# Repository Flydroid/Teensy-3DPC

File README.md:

# Teensy-3DPC 
is a 3D Printer Controller Board based on the Teensy 3.5 or 3.6.

Schematic and Layout are done in Eagle 

The hardware is still in development and this git used for sharing the development proceess.

#### Contribution to Think3dPrint3d and Esher3d for the DuetWifi Design on which, the Teensy-3DPC is partly based:

"Based on the DuetWifi by Think3dPrint3d and Esher3d, see www.duet3d.com for the original DuetWifi information. This reproduction/modification is not endorsed or supported in any way by Think3dPrint3d or Escher3d".

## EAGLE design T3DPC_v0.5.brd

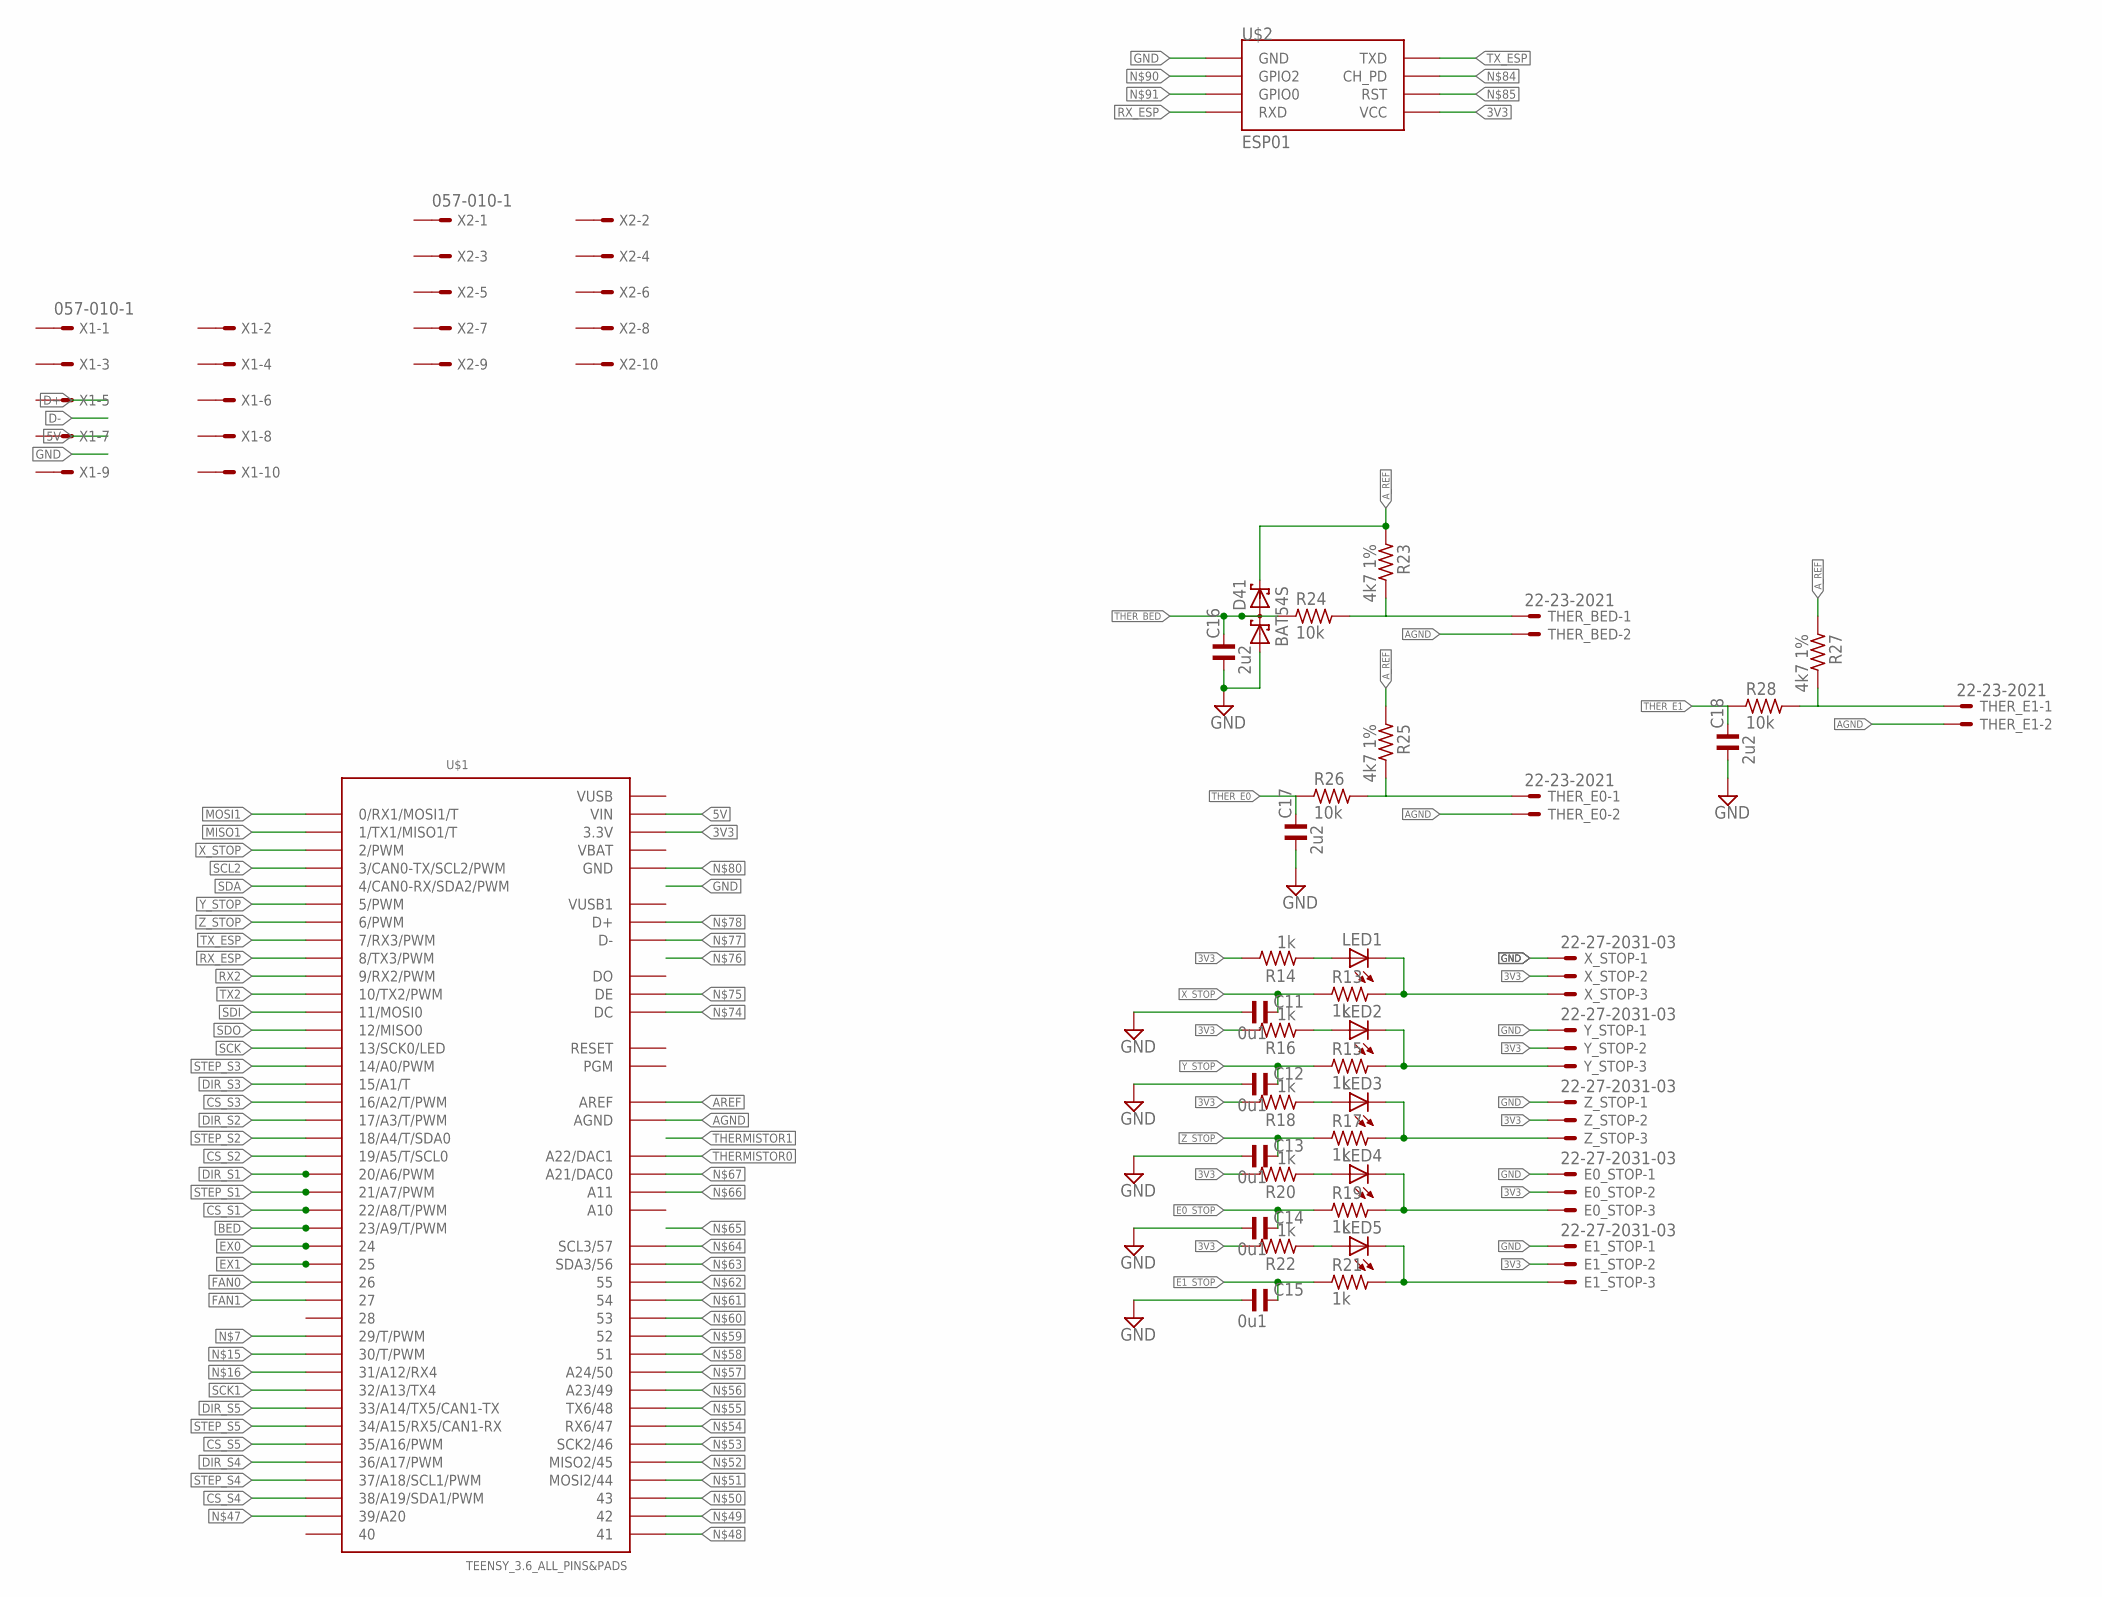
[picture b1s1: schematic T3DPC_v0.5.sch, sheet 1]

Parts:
C11, C12, C13, C14, C15: 0u1; C0805
C16, C17, C18: 2u2; C0805
D41: BAT54S; SOT23
E0_STOP, E1_STOP: 22-27-2031-03; 6410-03
LED1, LED2, LED3, LED4, LED5: LEDCHIPLED_1206; CHIPLED_1206
R13, R14, R15, R16, R17, R18, R19, R20, R21, R22: 1k; R0805
R23, R25, R27: 4k7 1%; R0805
R24, R26, R28: 10k; R0805
THER_BED: 22-23-2021
THER_E0, THER_E1: 22-23-2021
U$1: TEENSY_3.6_ALL_PINS&PADS
U$2: ESP01
X1, X2: 057-010-1
X_STOP: 22-27-2031-03; 6410-03
Y_STOP: 22-27-2031-03; 6410-03
Z_STOP: 22-27-2031-03; 6410-03

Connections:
3V3: E0_STOP.2, E1_STOP.2, R14.2, R16.2, R18.2, R20.2, R22.2, U$1.3.3V, U$1.3.3V2 (3.3V), U$1.3.3V3 (3.3V), U$1.3.3V4 (3.3V), U$2.VCC, X_STOP.2, Y_STOP.2, Z_STOP.2; also elsewhere on the board
5V: U$1.VIN; also elsewhere on the board
AGND: C16.1, C17.1, C18.1, D41.1 (A1), THER_BED.2, THER_E0.2, THER_E1.2, U$1.AGND
AREF: U$1.AREF
A_REF: D41.2 (C2), R23.1, R25.1, R27.1
BED: U$1.23/A9 (23/A9/T/PWM); also elsewhere on the board
CS_S1: U$1.22/A8 (22/A8/T/PWM); also elsewhere on the board
CS_S2: U$1.19/A5 (19/A5/T/SCL0); also elsewhere on the board
CS_S3: U$1.16/A2 (16/A2/T/PWM); also elsewhere on the board
CS_S4: U$1.38/A19 (38/A19/SDA1/PWM); also elsewhere on the board
CS_S5: U$1.35/A16 (35/A16/PWM); also elsewhere on the board
DIR_S1: U$1.20/A6 (20/A6/PWM); also elsewhere on the board
DIR_S2: U$1.17/A3 (17/A3/T/PWM); also elsewhere on the board
DIR_S3: U$1.15/A1 (15/A1/T); also elsewhere on the board
DIR_S4: U$1.36/A17 (36/A17/PWM); also elsewhere on the board
DIR_S5: U$1.33/A14 (33/A14/TX5/CAN1-TX); also elsewhere on the board
E0_STOP: C14.2, R19.1
E0_STOP_PORT: E0_STOP.3, LED4.C, R19.2
E1_STOP: C15.2, R21.1
E1_STOP_PORT: E1_STOP.3, LED5.C, R21.2
EX0: U$1.24; also elsewhere on the board
EX1: U$1.25; also elsewhere on the board
GND: C11.1, C12.1, C13.1, C14.1, C15.1, E0_STOP.1, E1_STOP.1, U$2.GND, X_STOP.1, Y_STOP.1, Z_STOP.1; also elsewhere on the board
MISO1: U$1.1 (1/TX1/MISO1/T)
MOSI1: U$1.0 (0/RX1/MOSI1/T)
unnamed: LED1.A, R14.1
unnamed: LED2.A, R16.1
unnamed: LED3.A, R18.1
unnamed: LED4.A, R20.1
unnamed: LED5.A, R22.1
unnamed: R25.2, R26.2, THER_E0.1
unnamed: R23.2, R24.2, THER_BED.1
unnamed: R27.2, R28.2, THER_E1.1
unnamed: U$1.GND, U$1.GND1 (GND), U$1.GND2 (GND), U$1.GND3 (GND), U$1.GND4 (GND), U$1.GND5 (GND), U$1.GND6 (GND)
RX2: U$1.9 (9/RX2/PWM)
RX_ESP: U$1.8 (8/TX3/PWM), U$2.RX (RXD)
SCK: U$1.13 (13/SCK0/LED); also elsewhere on the board
SCK1: U$1.32/A13 (32/A13/TX4)
SCL2: U$1.3 (3/CAN0-TX/SCL2/PWM)
SDA: U$1.4 (4/CAN0-RX/SDA2/PWM)
SDI: U$1.11 (11/MOSI0); also elsewhere on the board
SDO: U$1.12 (12/MISO0); also elsewhere on the board
STEP_S1: U$1.21/A7 (21/A7/PWM); also elsewhere on the board
STEP_S2: U$1.18/A4 (18/A4/T/SDA0); also elsewhere on the board
STEP_S3: U$1.14/A0 (14/A0/PWM); also elsewhere on the board
STEP_S4: U$1.37/A18 (37/A18/SCL1/PWM); also elsewhere on the board
STEP_S5: U$1.34/A15 (34/A15/RX5/CAN1-RX); also elsewhere on the board
THERMISTOR0: U$1.A22 (A22/DAC1)
THER_BED: C16.2, D41.3 (C1A2), R24.1
THER_E0: C17.2, R26.1
THER_E1: C18.2, R28.1
TX2: U$1.10 (10/TX2/PWM)
TX_ESP: U$1.7 (7/RX3/PWM), U$2.TX (TXD)
VBAT: U$1.VBAT
VUSB: U$1.VUSB
VUSB1: U$1.VUSB1
X_STOP: C11.2, R13.1, U$1.2 (2/PWM)
X_STOP_PORT: LED1.C, R13.2, X_STOP.3
Y_STOP: C12.2, R15.1, U$1.5 (5/PWM)
Y_STOP_PORT: LED2.C, R15.2, Y_STOP.3
Z_STOP: C13.2, R17.1, U$1.6 (6/PWM)
Z_STOP_PORT: LED3.C, R17.2, Z_STOP.3

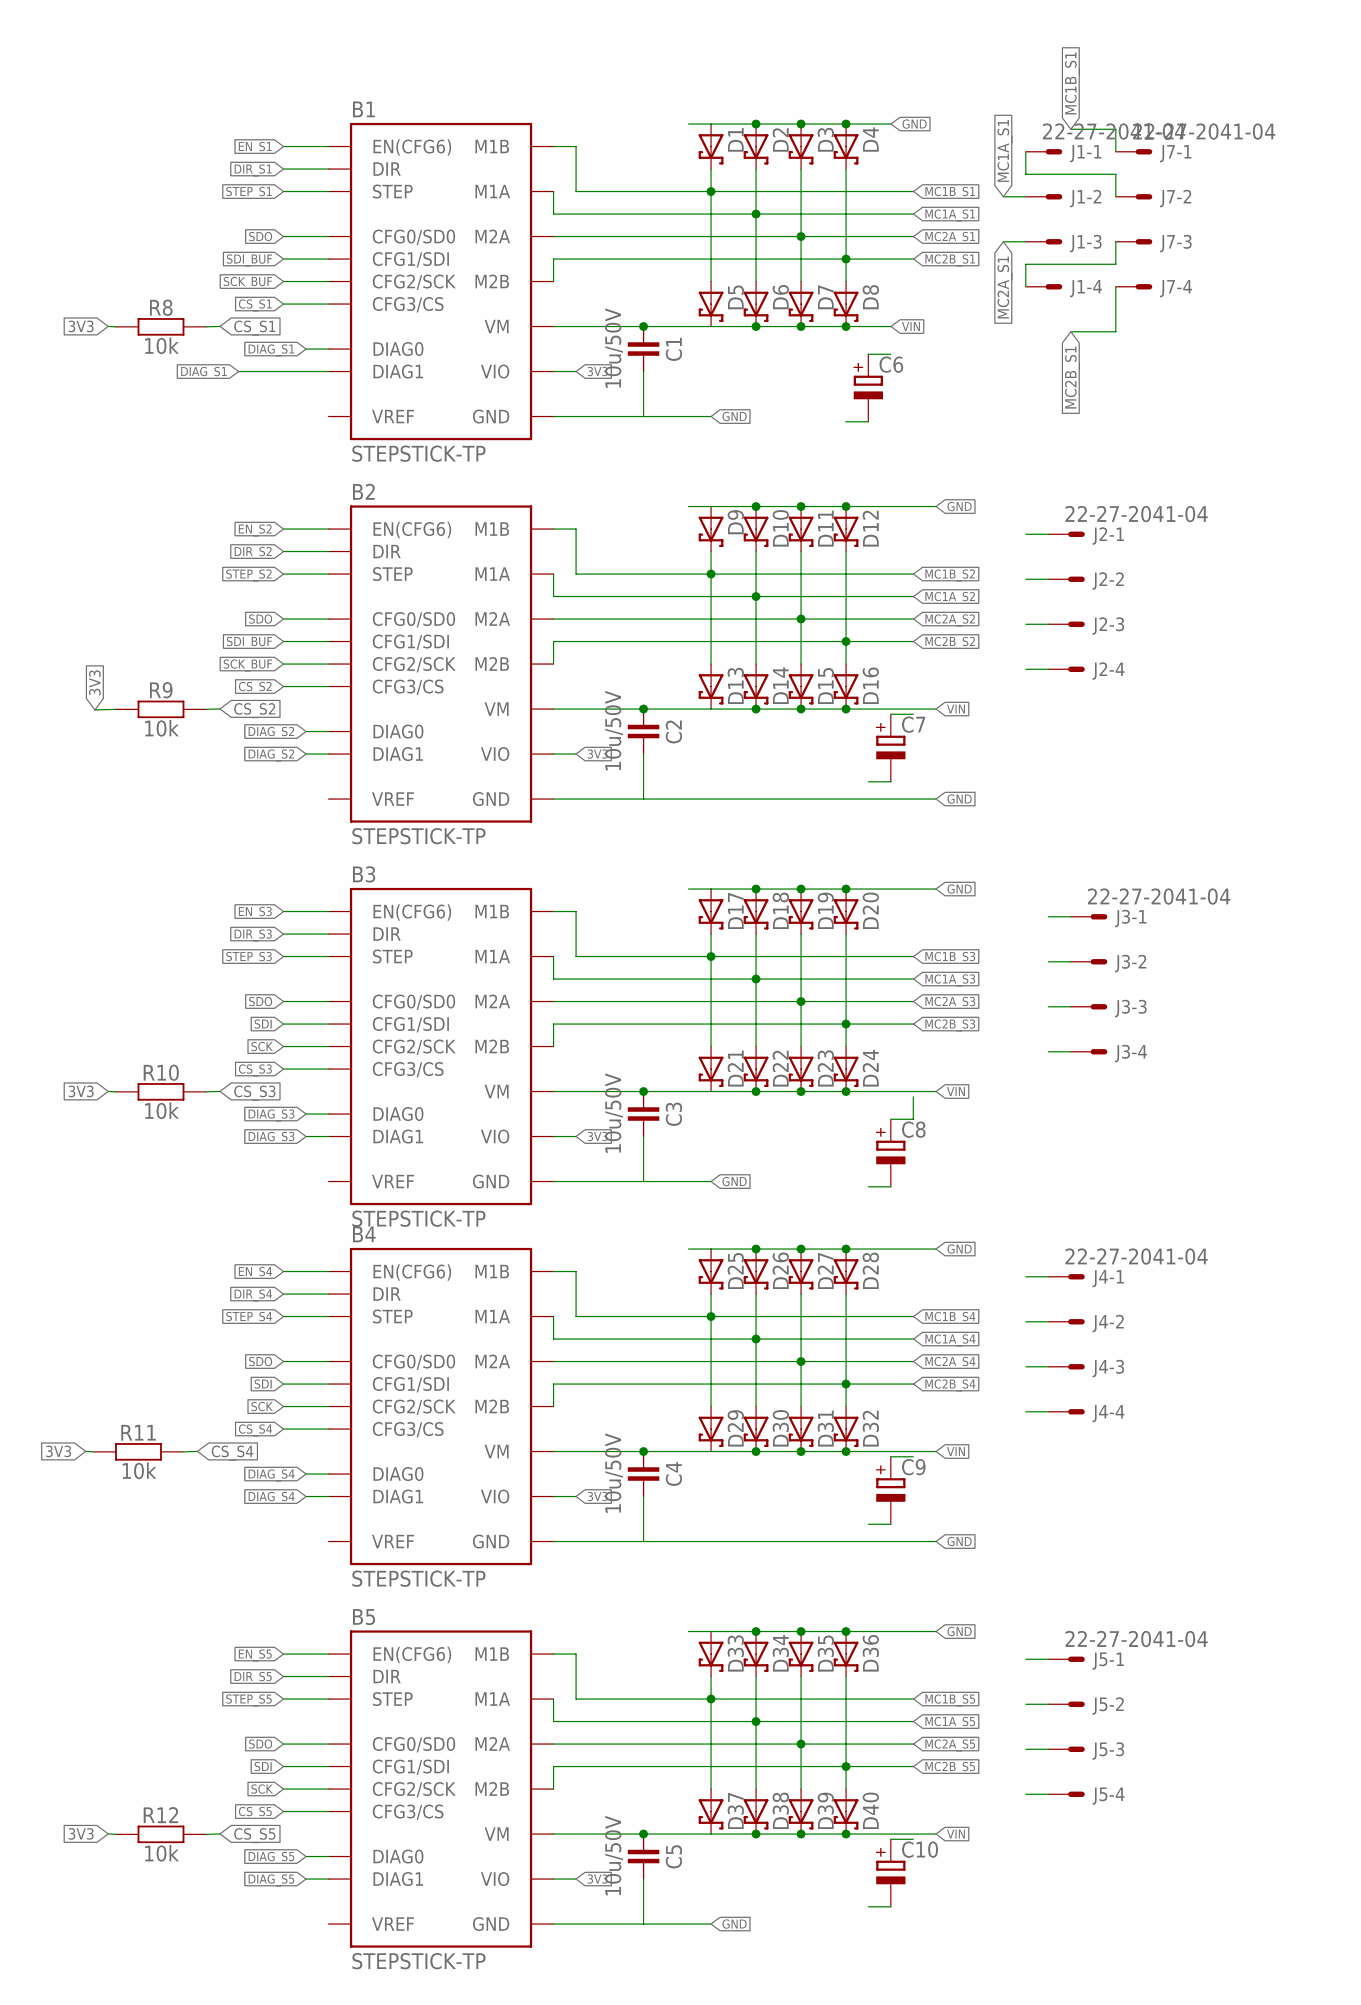
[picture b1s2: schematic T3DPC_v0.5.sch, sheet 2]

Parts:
B1, B2, B3, B4, B5: STEPSTICK-TP; STEPSTICK_TP
C1, C2, C3, C4, C5: 10u/50V; C1210
C6, C7, C8, C9, C10: CPOL-EU153CLV-0505; 153CLV-0505
D1, D2, D3, D4, D5, D6, D7, D8, D9, D10, D11, D12, D13, D14, D15, D16, D17, D18, D19, D20, D21, D22, D23, D24, D25, D26, D27, D28, D29, D30, D31, D32, D33, D34, D35, D36, D37, D38, D39, D40: D_SCHOTTKY-SMA; SMA_DO214AC
J1, J2, J3, J4, J5, J7: 22-27-2041-04; 6410-04
R8, R9, R10, R11, R12: 10k; C0805

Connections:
3V3: B1.VIO, B2.VIO, B3.VIO, B4.VIO, B5.VIO, R8.1, R9.1, R10.1, R11.1, R12.1; also elsewhere on the board
CS_S1: B1.CFG3 (CFG3/CS), R8.2; also elsewhere on the board
CS_S2: B2.CFG3 (CFG3/CS), R9.2; also elsewhere on the board
CS_S3: B3.CFG3 (CFG3/CS), R10.2; also elsewhere on the board
CS_S4: B4.CFG3 (CFG3/CS), R11.2; also elsewhere on the board
CS_S5: B5.CFG3 (CFG3/CS), R12.2; also elsewhere on the board
DIAG_S1: B1.DIAG0, B1.DIAG1
DIAG_S2: B2.DIAG0, B2.DIAG1
DIAG_S3: B3.DIAG0, B3.DIAG1
DIAG_S4: B4.DIAG0, B4.DIAG1
DIAG_S5: B5.DIAG0, B5.DIAG1
DIR_S1: B1.DIR; also elsewhere on the board
DIR_S2: B2.DIR; also elsewhere on the board
DIR_S3: B3.DIR; also elsewhere on the board
DIR_S4: B4.DIR; also elsewhere on the board
DIR_S5: B5.DIR; also elsewhere on the board
EN_S1: B1.EN (EN(CFG6))
EN_S2: B2.EN (EN(CFG6))
EN_S3: B3.EN (EN(CFG6))
EN_S4: B4.EN (EN(CFG6))
EN_S5: B5.EN (EN(CFG6))
GND: B1.GND@1 (GND), B1.GND@2 (GND), B2.GND@1 (GND), B2.GND@2 (GND), B3.GND@1 (GND), B3.GND@2 (GND), B4.GND@1 (GND), B4.GND@2 (GND), B5.GND@1 (GND), B5.GND@2 (GND), C1.2, C2.2, C3.2, C4.2, C5.2, C6.-, C7.-, C8.-, C9.-, C10.-, D1.A, D2.A, D3.A, D4.A, D9.A, D10.A, D11.A, D12.A, D17.A, D18.A, D19.A, D20.A, D25.A, D26.A, D27.A, D28.A, D33.A, D34.A, D35.A, D36.A; also elsewhere on the board
MC1A_S1: B1.M1A, D2.C, D6.A, J1.2
MC1A_S2: B2.M1A, D10.C, D14.A, J2.2
MC1A_S3: B3.M1A, D18.C, D22.A, J3.2
MC1A_S4: B4.M1A, D26.C, D30.A, J4.2
MC1A_S5: B5.M1A, D34.C, D38.A, J5.2
MC1B_S1: B1.M1B, D1.C, D5.A, J7.1
MC1B_S2: B2.M1B, D9.C, D13.A, J2.1
MC1B_S3: B3.M1B, D17.C, D21.A, J3.1
MC1B_S4: B4.M1B, D25.C, D29.A, J4.1
MC1B_S5: B5.M1B, D33.C, D37.A, J5.1
MC2A_S1: B1.M2A, D3.C, D7.A, J1.3
MC2A_S2: B2.M2A, D11.C, D15.A, J2.3
MC2A_S3: B3.M2A, D19.C, D23.A, J3.3
MC2A_S4: B4.M2A, D27.C, D31.A, J4.3
MC2A_S5: B5.M2A, D35.C, D39.A, J5.3
MC2B_S1: B1.M2B, D4.C, D8.A, J7.4
MC2B_S2: B2.M2B, D12.C, D16.A, J2.4
MC2B_S3: B3.M2B, D20.C, D24.A, J3.4
MC2B_S4: B4.M2B, D28.C, D32.A, J4.4
MC2B_S5: B5.M2B, D36.C, D40.A, J5.4
unnamed: J1.4, J7.3
unnamed: J1.1, J7.2
SCK: B3.CFG2 (CFG2/SCK), B4.CFG2 (CFG2/SCK), B5.CFG2 (CFG2/SCK); also elsewhere on the board
SCK_BUF: B1.CFG2 (CFG2/SCK), B2.CFG2 (CFG2/SCK)
SDI: B3.CFG1 (CFG1/SDI), B4.CFG1 (CFG1/SDI), B5.CFG1 (CFG1/SDI); also elsewhere on the board
SDI_BUF: B1.CFG1 (CFG1/SDI), B2.CFG1 (CFG1/SDI)
SDO: B1.NC/CFG0 (CFG0/SD0), B2.NC/CFG0 (CFG0/SD0), B3.NC/CFG0 (CFG0/SD0), B4.NC/CFG0 (CFG0/SD0), B5.NC/CFG0 (CFG0/SD0); also elsewhere on the board
STEP_S1: B1.STEP; also elsewhere on the board
STEP_S2: B2.STEP; also elsewhere on the board
STEP_S3: B3.STEP; also elsewhere on the board
STEP_S4: B4.STEP; also elsewhere on the board
STEP_S5: B5.STEP; also elsewhere on the board
VIN: B1.VM, B2.VM, B3.VM, B4.VM, B5.VM, C1.1, C2.1, C3.1, C4.1, C5.1, C6.+, C7.+, C8.+, C9.+, C10.+, D5.C, D6.C, D7.C, D8.C, D13.C, D14.C, D15.C, D16.C, D21.C, D22.C, D23.C, D24.C, D29.C, D30.C, D31.C, D32.C, D37.C, D38.C, D39.C, D40.C; also elsewhere on the board

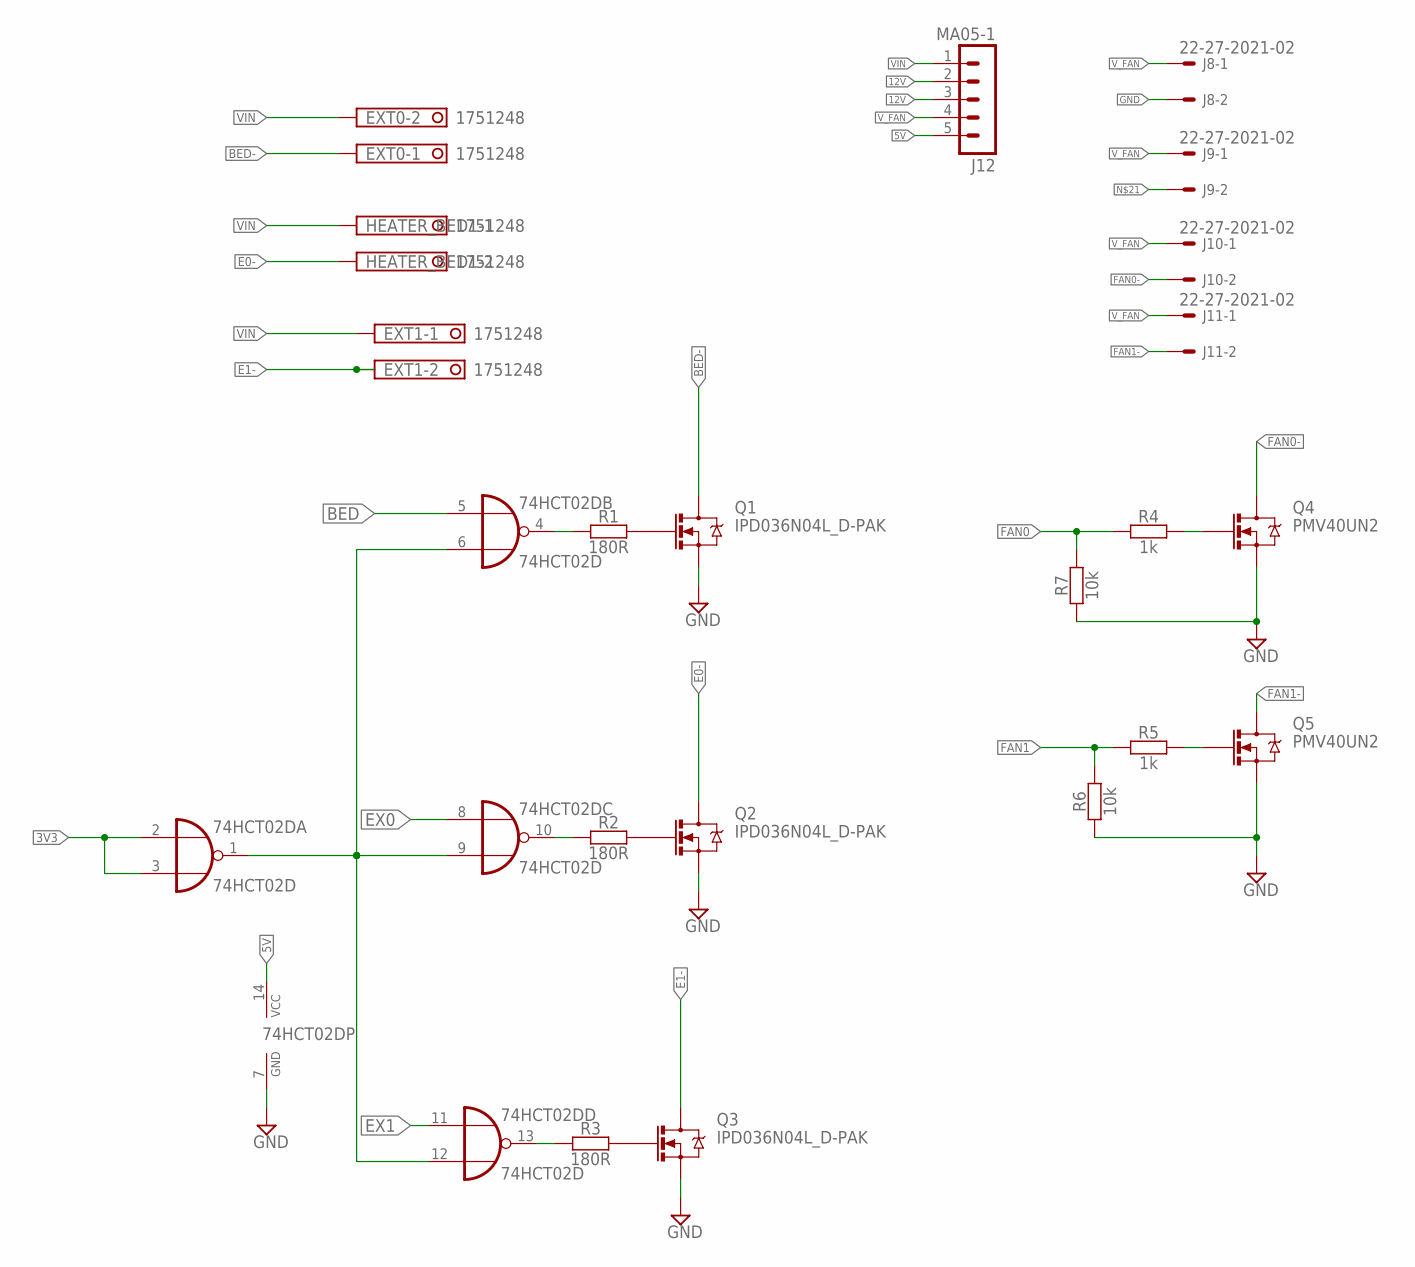
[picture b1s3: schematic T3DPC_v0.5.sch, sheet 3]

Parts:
74HCT02D: 74HCT02D; SO14
EXT0, EXT1: 1751248
HEATER_BED1: 1751248
J8, J9, J10, J11: 22-27-2021-02; 6410-02
J12: MA05-1
Q1, Q2, Q3: IPD036N04L_D-PAK; D-PAK_TO252AA
Q4, Q5: PMV40UN2; SOT23-3
R1, R2, R3: 180R; C0805
R4, R5: 1k; C0805
R6, R7: 10k; C0805

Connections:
3V3: 74HCT02D.2 (I0), 74HCT02D.3 (I1); also elsewhere on the board
5V: 74HCT02D.14 (VCC), J12.5; also elsewhere on the board
12V: J12.2, J12.3; also elsewhere on the board
BED: 74HCT02D.5 (I0); also elsewhere on the board
BED-: EXT0.1, Q1.2 (D)
E0-: HEATER_BED1.2, Q2.2 (D)
E1-: EXT1.2, Q3.2 (D)
EX0: 74HCT02D.8 (I0); also elsewhere on the board
EX1: 74HCT02D.11 (I0); also elsewhere on the board
FAN0: R4.1, R7.2
FAN0-: J10.2, Q4.3 (D)
FAN1: R5.1, R6.2
FAN1-: J11.2, Q5.3 (D)
GND: 74HCT02D.7 (GND), J8.2, Q1.3 (S), Q2.3 (S), Q3.3 (S), Q4.2 (S), Q5.2 (S), R6.1, R7.1; also elsewhere on the board
unnamed: Q1.1 (G), R1.2
unnamed: Q2.1 (G), R2.2
unnamed: Q3.1 (G), R3.2
unnamed: 74HCT02D.4 (O), R1.1
unnamed: 74HCT02D.10 (O), R2.1
unnamed: 74HCT02D.13 (O), R3.1
unnamed: 74HCT02D.1 (O), 74HCT02D.6 (I1), 74HCT02D.9 (I1), 74HCT02D.12 (I1)
unnamed: Q4.1 (G), R4.2
unnamed: Q5.1 (G), R5.2
VIN: EXT0.2, EXT1.1, HEATER_BED1.1, J12.1; also elsewhere on the board
V_FAN: J8.1, J9.1, J10.1, J11.1, J12.4

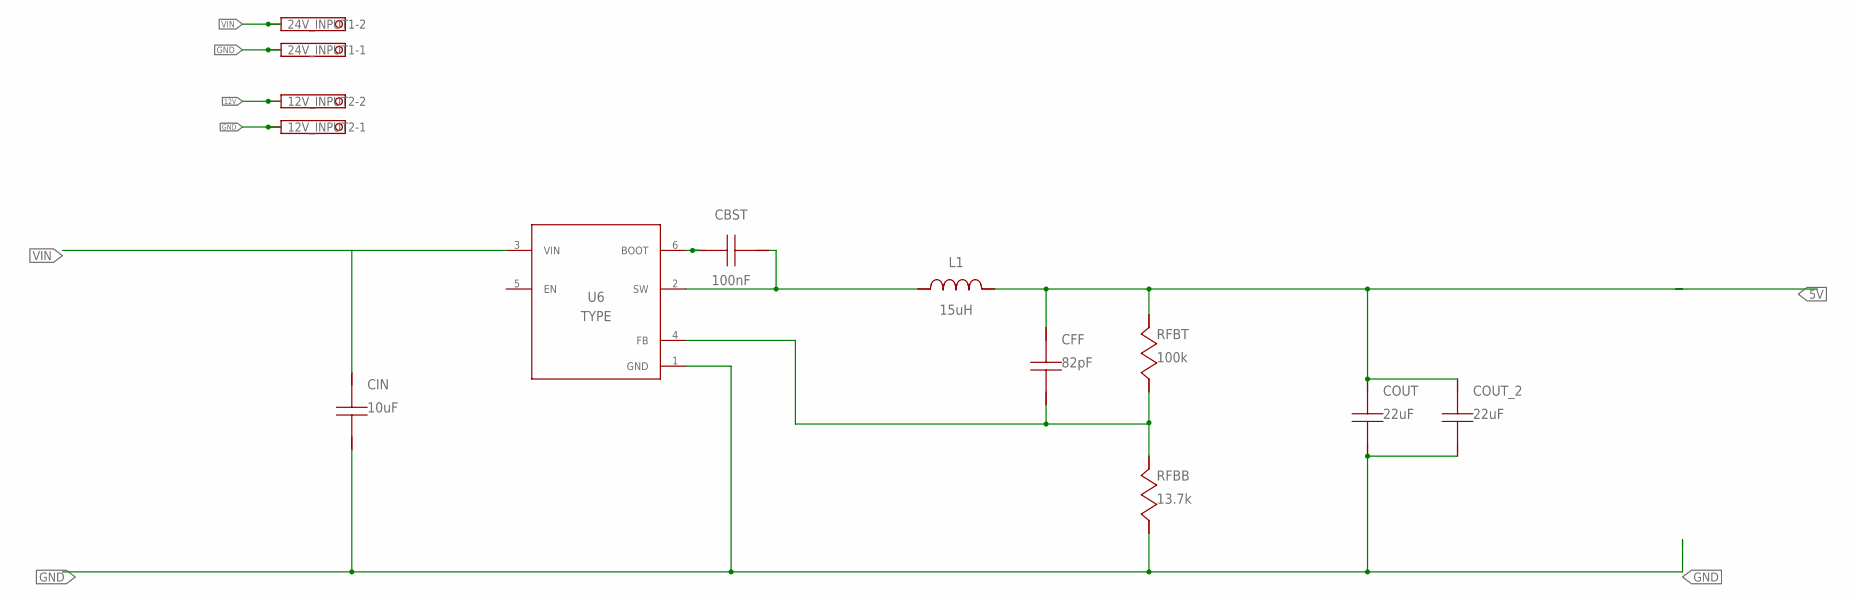
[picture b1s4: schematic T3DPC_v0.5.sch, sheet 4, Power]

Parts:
12V_INPUT2, 24V_INPUT1: 1751248
CBST: 100nF; 0805
CFF: 82pF; 0805
CIN: 10uF; 1206_180
COUT: 22uF; 1812
COUT_2: 22uF; 1812
L1: 15uH; VLP8040
RFBB: 13.7k; 0805
RFBT: 100k; 0805
U6: Value; DDC0006A_N

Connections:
1: CBST.1, U6.6 (BOOT)
2: CFF.2, RFBB.1, RFBT.2, U6.4 (FB)
3: CBST.2, L1.1, U6.2 (SW)
5V: CFF.1, COUT.1, COUT_2.1, L1.2, RFBT.1; also elsewhere on the board
12V: 12V_INPUT2.2; also elsewhere on the board
GND: 12V_INPUT2.1, 24V_INPUT1.1, CIN.2, COUT.2, COUT_2.2, RFBB.2, U6.1 (GND); also elsewhere on the board
VIN: 24V_INPUT1.2, U6.3 (VIN); also elsewhere on the board

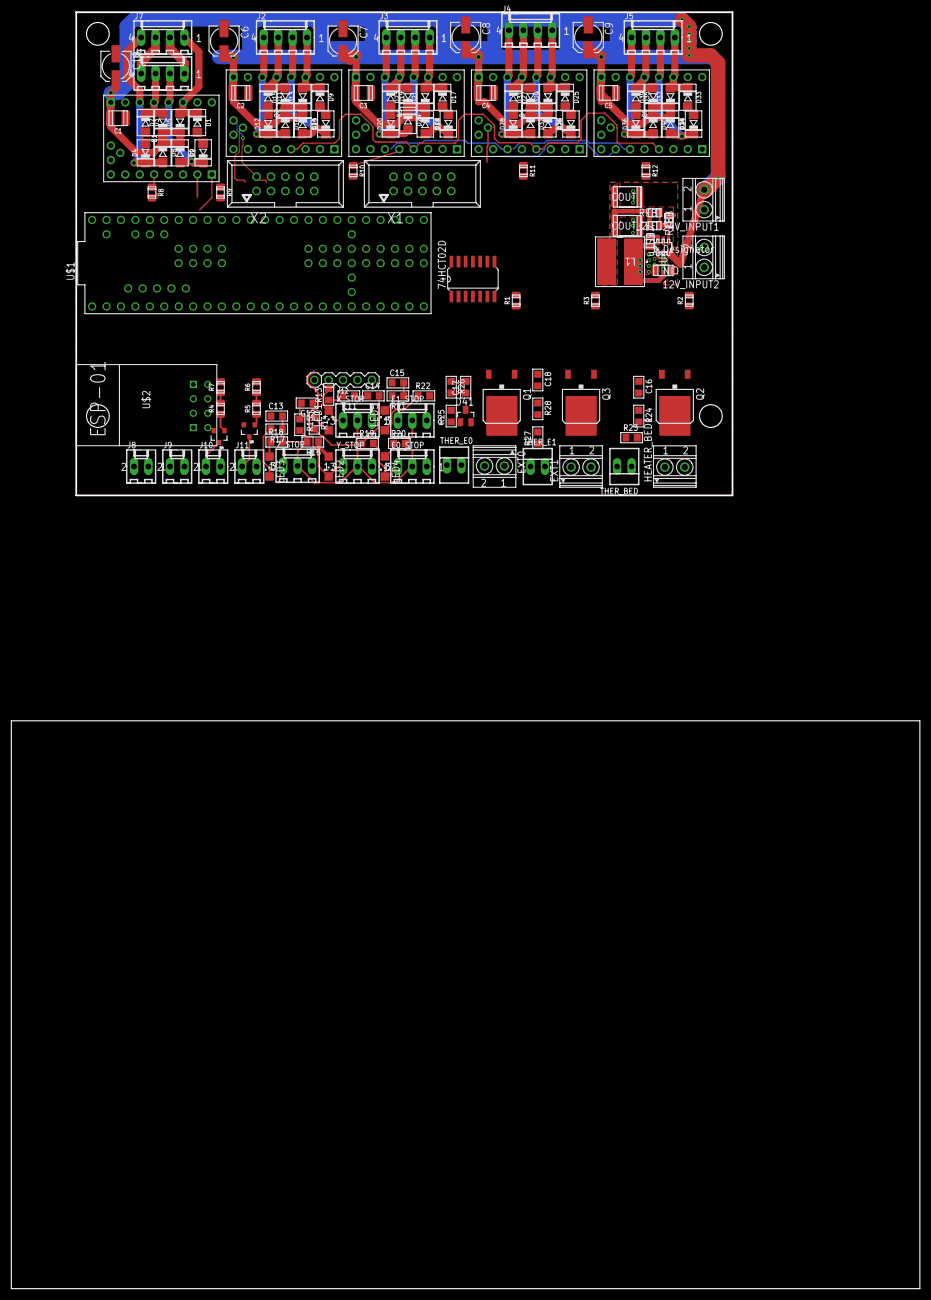
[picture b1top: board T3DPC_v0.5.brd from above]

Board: 2 copper layers, 159.7 x 224.6 mm, 140 parts (0 on the bottom side), 101 nets.

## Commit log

2017-01-15 :neckbeard: Added .gitattributes
2017-01-23 Featurer Overview added
2017-02-06 update schematic and board layout
2017-12-17 Create LICENSE
2017-12-17 Update LICENSE
2018-01-06 Update Schematics and Layout

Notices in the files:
parts and their libraries:
rc-master-smd: Copyright (C) 2007-2008, Bob Starr
